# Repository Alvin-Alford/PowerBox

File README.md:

#  PowerBox

> An all-in-one power solution for cyberdecks and portable embedded systems.

PowerBox is my custom-designed PCB that handles USB-C Power Delivery input, dual-cell lithium battery management, balance charging, and regulated power output, all in a single compact board. Designed to push up to **36W** of power to whatever you throw at it.

---

## Overview

*PowerBox was built to power DIY cyberdecks and portable computing projects that need more juice than a standard battery banks can provide.*

---

## Components

PowerBox is built around **7 core subsystems**:

### 1. USB-C Power Delivery Input
A USB-C port paired with a **PD sink controller** that negotiates **12V** from a PD-capable charger. At full load the circuit can draw up to **36W** which is well beyond what standard 5V USB can supply.

### 2. Dual Buck DC-DC Converters (×2)
Two **TPS54620** synchronous step-down converters provide regulated output voltages. The TPS54620 is a 6A, 17V capable device giving plenty of headroom for demanding loads.

### 3. Ideal Diode Circuits (×2)
When USB-C power is present, the battery-fed bucks are switched off to prevent backfeeding the charger. This creates a condition where the buck converter inputs can see negative voltages which is outside their rated range. The ideal diode circuits clamp this safely, acting as electronic diodes with near-zero forward voltage drop.

### 4. BMS Circuit (DW01A)
A battery management system built around the **DW01A** which is a popular and proven lithium-ion protection IC. Handles over-charge, over-discharge, and short-circuit protection for the cell pack.

### 5. 2S Balance Charger (BQ2588RGER)
A proper **2-series balance charger** using TI's **BQ2588RGER**, capable of up to **2A** charge current. Keeps both cells at equal state-of-charge for longevity and safety.

---

##  PCB

The PCB design files are in the [`PowerBox_PCB/`](./PowerBox_PCB) directory. Output gerbers and fabrication files are in [`Output/`](./Output).

---

## Design Logic

```
USB-C PD (12V, 36W)
        │
        ├──► Buck 1 (TPS54620) ──► Ideal Diode ──► Output Rail A
        │
        ├──► Buck 2 (TPS54620) ──► Ideal Diode ──► Output Rail B
        │
        └──► BQ2588RGER Balance Charger ──► 2S Li-Ion Pack
                                                  │
                                              DW01A BMS
                                                  │
                                            Battery Output
```

**Why did I choose 36W / USB-C PD?**

A 2S lithium pack needs to charge while simultaneously powering the system. At full system load, 15W standard USB-C isn't enough, it can't even charge an open MacBook. Requesting **12V via PD** and pulling up to **3A** gives the 36W headroom needed to charge the battery *and* run the load at the same time.

**Why two cells?**

More cells = more capacity. More capacity = the circuit can sustain high loads without the cells entering stress territory. A single-cell design at 36W draw would be asking for trouble (and possibly a fire).

---

## Repository Structure

```
PowerBox/
├── Notes/           # Design notes and calculations
├── Output/          # Gerber files and fabrication outputs
├── Parts/           # Bill of materials and component info
└── PowerBox_PCB/    # KiCad / PCB design files
```

---

## Key ICs

| Component | Part Number | Function |
|-----------|------------|----------|
| Buck Converter | TPS54620 | 6A, 17V synchronous step-down |
| Balance Charger | BQ2588RGER | 2S Li-Ion balance charger, 2A |
| BMS Controller | DW01A | Li-Ion protection IC |
| PD Sink | *(see Parts/)* | USB-C PD 12V negotiation |

---

## Zine

---

## License

See [LICENSE](./LICENSE) for details.

---

*Built by [Alvin-Alford](https://github.com/Alvin-Alford)*

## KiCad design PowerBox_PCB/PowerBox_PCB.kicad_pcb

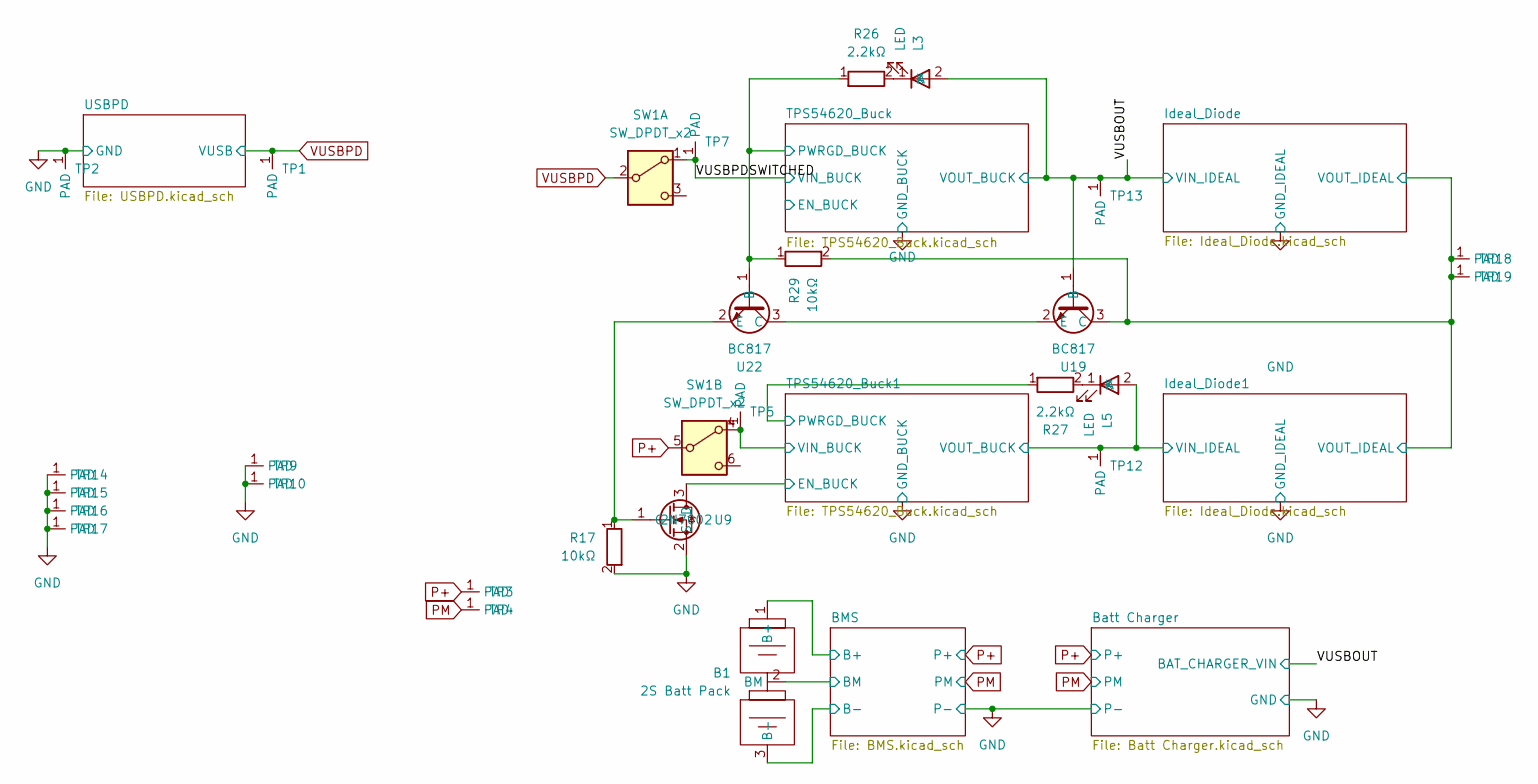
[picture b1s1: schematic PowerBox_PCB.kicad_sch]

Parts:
B1: 2S Batt Pack
L3, L5: LED; LED_0805_2012Metric_Pad1.15x1.40mm_HandSolder
R17, R29: 10kΩ; R_0805_2012Metric_Pad1.20x1.40mm_HandSolder
R26, R27: 2.2kΩ; R_0805_2012Metric_Pad1.20x1.40mm_HandSolder
SW1: SW_DPDT_x2; SwitchPads
TP1, TP2, TP3, TP4, TP5, TP7, TP9, TP10, TP12, TP13: PAD-2x2
TP14, TP15, TP16, TP17: M3-Pad
TP18, TP19: PAD-2x2-ThroughHole
U9: 2N7002; SOT-23
U19, U22: BC817; SOT-23

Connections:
/BMS/B-: B1.3 (B-); also elsewhere on the board
/BMS/BM: B1.2 (BM); also elsewhere on the board
/Ideal_Diode1/VIN_IDEAL: L5.2 (A), TP12.1 (PAD_1); also elsewhere on the board
/Ideal_Diode/VOUT_IDEAL: R29.2, TP18.1 (PAD_1), TP19.1 (PAD_1), U19.3 (C); also elsewhere on the board
/TPS54620_Buck1/EN_BUCK: U9.3 (D); also elsewhere on the board
/TPS54620_Buck1/PWRGD_BUCK: R27.1; also elsewhere on the board
/TPS54620_Buck1/VIN_BUCK: SW1.4 (A), TP5.1 (PAD_1); also elsewhere on the board
/TPS54620_Buck/PWRGD_BUCK: R26.1, R29.1, U22.1 (B); also elsewhere on the board
/VUSBOUT: L3.2 (A), TP13.1 (PAD_1), U19.1 (B); also elsewhere on the board
/VUSBPDSWITCHED: SW1.1 (A), TP7.1 (PAD_1); also elsewhere on the board
GND: R17.2, TP2.1 (PAD_1), TP9.1 (PAD_1), TP10.1 (PAD_1), TP14.1 (PAD_1), TP15.1 (PAD_1), TP16.1 (PAD_1), TP17.1 (PAD_1), U9.2 (S); also elsewhere on the board
unnamed: L3.1 (K), R26.2
unnamed: L5.1 (K), R27.2
unnamed: U19.2 (E), U22.3 (C)
unnamed: R17.1, U9.1 (G), U22.2 (E)
P+: B1.1 (B+), SW1.5 (B), TP3.1 (PAD_1); also elsewhere on the board
PM: TP4.1 (PAD_1); also elsewhere on the board
VUSBPD: SW1.2 (B), TP1.1 (PAD_1); also elsewhere on the board

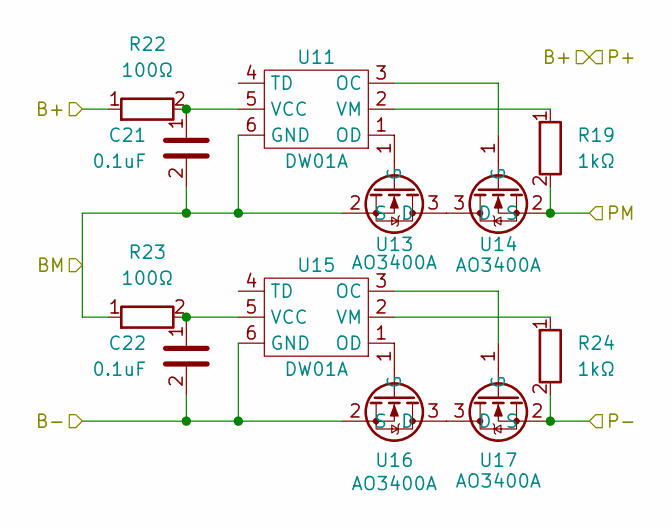
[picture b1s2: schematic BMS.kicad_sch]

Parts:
C21, C22: 0.1uF; C_0805_2012Metric_Pad1.18x1.45mm_HandSolder
R19, R24: 1kΩ; R_0805_2012Metric_Pad1.20x1.40mm_HandSolder
R22, R23: 100Ω; R_0805_2012Metric_Pad1.20x1.40mm_HandSolder
U11, U15: DW01A; SOT-23-6_Handsoldering
U13, U14, U16, U17: AO3400A; SOT-23_Handsoldering

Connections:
/BMS/B-: C22.2, U15.6 (GND), U16.2 (S); also elsewhere on the board
/BMS/BM: C21.2, R23.1, U11.6 (GND), U13.2 (S); also elsewhere on the board
GND: R24.2, U17.2 (S); also elsewhere on the board
unnamed: U11.3 (OC), U14.1 (G)
unnamed: U11.1 (OD), U13.1 (G)
unnamed: C21.1, R22.2, U11.5 (VCC)
unnamed: R19.1, U11.2 (VM)
unnamed: U13.3 (D), U14.3 (D)
unnamed: U15.3 (OC), U17.1 (G)
unnamed: U15.1 (OD), U16.1 (G)
unnamed: C22.1, R23.2, U15.5 (VCC)
unnamed: R24.1, U15.2 (VM)
unnamed: U16.3 (D), U17.3 (D)
P+: R22.1; also elsewhere on the board
PM: R19.2, U14.2 (S); also elsewhere on the board

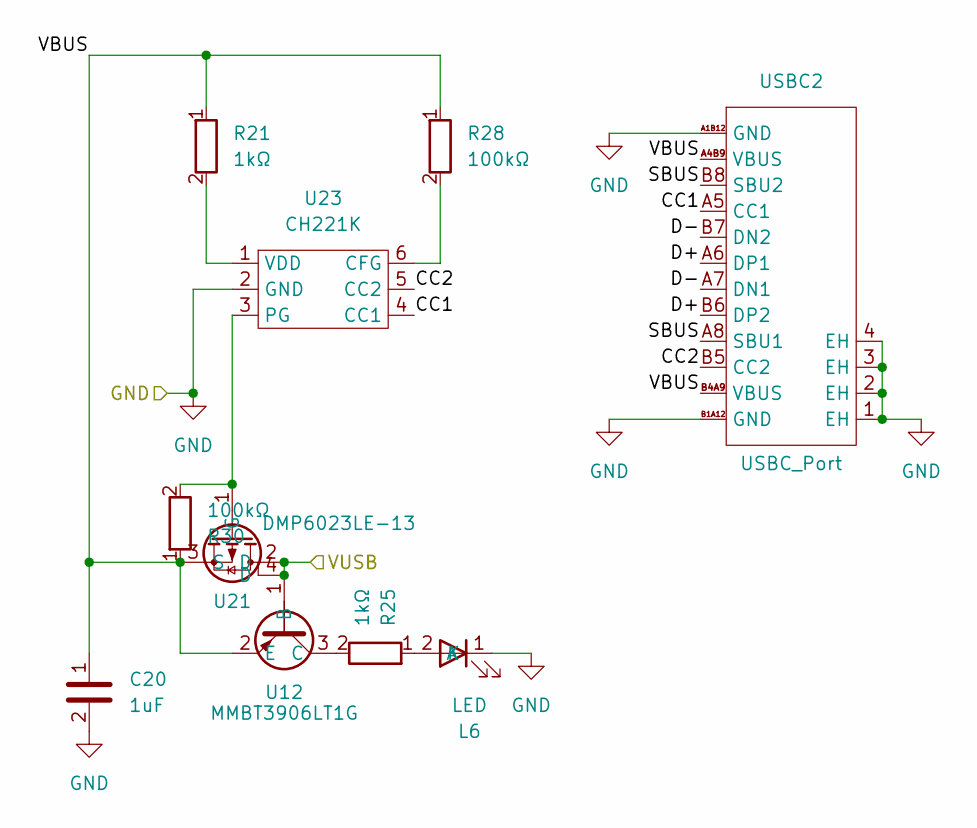
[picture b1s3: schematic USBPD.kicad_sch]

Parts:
C20: 1uF; C_0805_2012Metric_Pad1.18x1.45mm_HandSolder
L6: LED; LED_0805_2012Metric_Pad1.15x1.40mm_HandSolder
R21, R25: 1kΩ; R_0805_2012Metric_Pad1.20x1.40mm_HandSolder
R28, R30: 100kΩ; R_0805_2012Metric_Pad1.20x1.40mm_HandSolder
U12: MMBT3906LT1G; SOT-23
U21: DMP6023LE-13; SOT-223
U23: CH221K; SOT-23-6
USBC2: USBC_Port; USB-C_SMD-TYPE-C-31-M-12_1; Manufacturer Part TYPE-C-31-M-12; LCSC Part Name Type-C 母 卧贴

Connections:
/USBPD/CC1: U23.4 (CC1), USBC2.A5 (CC1)
/USBPD/CC2: U23.5 (CC2), USBC2.B5 (CC2)
/USBPD/D+: USBC2.A6 (DP1), USBC2.B6 (DP2)
/USBPD/D-: USBC2.A7 (DN1), USBC2.B7 (DN2)
/USBPD/SBUS: USBC2.A8 (SBU1), USBC2.B8 (SBU2)
/USBPD/VBUS: C20.1, R21.1, R28.1, R30.1, U12.2 (E), U21.3 (S), USBC2.A4B9 (VBUS), USBC2.B4A9 (VBUS)
GND: C20.2, L6.1 (K), U23.2 (GND), USBC2.1 (EH), USBC2.2 (EH), USBC2.3 (EH), USBC2.4 (EH), USBC2.A1B12 (GND), USBC2.B1A12 (GND); also elsewhere on the board
unnamed: L6.2 (A), R25.1
unnamed: R25.2, U12.3 (C)
unnamed: R30.2, U21.1 (G), U23.3 (PG)
unnamed: R28.2, U23.6 (CFG)
unnamed: R21.2, U23.1 (VDD)
VUSBPD: U12.1 (B), U21.2 (D), U21.4 (D); also elsewhere on the board

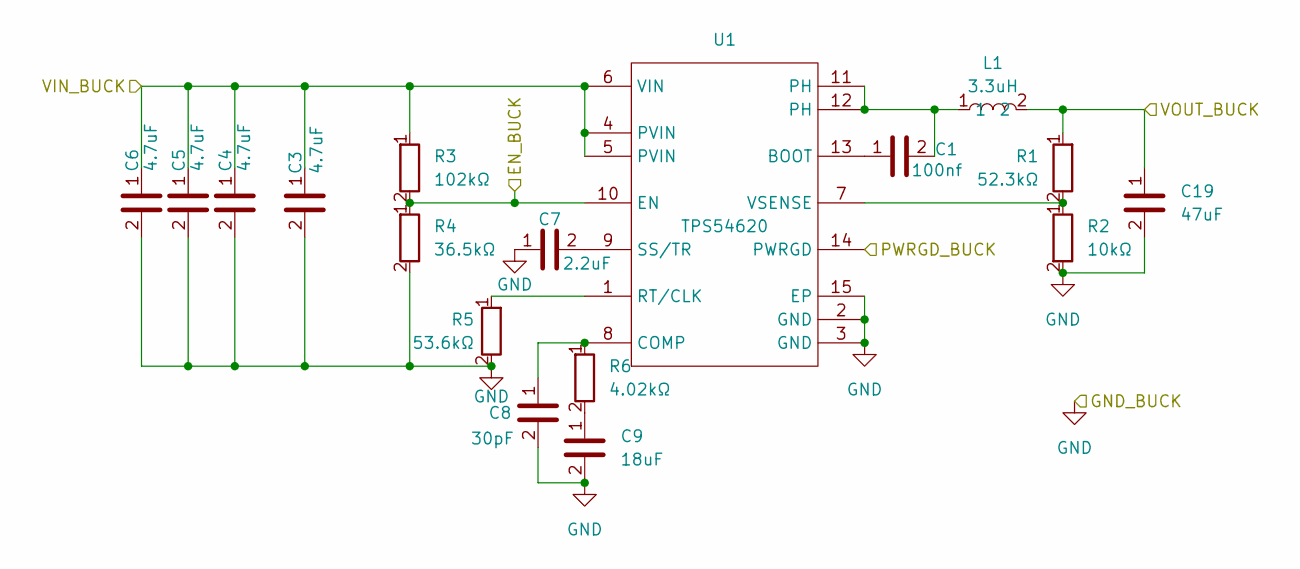
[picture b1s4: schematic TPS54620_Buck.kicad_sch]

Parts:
C1: 100nf; C_0805_2012Metric_Pad1.18x1.45mm_HandSolder
C3, C4, C5, C6: 4.7uF; C_0805_2012Metric_Pad1.18x1.45mm_HandSolder
C7: 2.2uF; C_0805_2012Metric_Pad1.18x1.45mm_HandSolder
C8: 30pF; C_0805_2012Metric_Pad1.18x1.45mm_HandSolder
C9: 18uF; C_0805_2012Metric_Pad1.18x1.45mm_HandSolder
C19: 47uF; C_1210_3225Metric_Pad1.33x2.70mm_HandSolder
L1: 3.3uH; IND-SMD_L8.5-W8.0_PSPMAA0803H-330M-ANP
R1: 52.3kΩ; R_0805_2012Metric_Pad1.20x1.40mm_HandSolder
R2: 10kΩ; R_0805_2012Metric_Pad1.20x1.40mm_HandSolder
R3: 102kΩ; R_0805_2012Metric_Pad1.20x1.40mm_HandSolder
R4: 36.5kΩ; R_0805_2012Metric_Pad1.20x1.40mm_HandSolder
R5: 53.6kΩ; R_0805_2012Metric_Pad1.20x1.40mm_HandSolder
R6: 4.02kΩ; R_0805_2012Metric_Pad1.20x1.40mm_HandSolder
U1: TPS54620; VQFN-14_L3.5-W3.5-P0.50-TL-EP_TPS54622RHLT; Manufacturer Part TPS54620RHLR; LCSC Part Name 17V输入6A同步降压转换器

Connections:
/TPS54620_Buck/EN_BUCK: R3.2, R4.1, U1.10 (EN)
/TPS54620_Buck/PWRGD_BUCK: U1.14 (PWRGD); also elsewhere on the board
/VUSBOUT: C19.1, L1.2, R1.1; also elsewhere on the board
/VUSBPDSWITCHED: C3.1, C4.1, C5.1, C6.1, R3.1, U1.4 (PVIN), U1.5 (PVIN), U1.6 (VIN); also elsewhere on the board
GND: C3.2, C4.2, C5.2, C6.2, C7.1, C8.2, C9.2, C19.2, R2.2, R4.2, R5.2, U1.2 (GND), U1.3 (GND), U1.15 (EP); also elsewhere on the board
unnamed: C1.2, L1.1, U1.11 (PH), U1.12 (PH)
unnamed: C9.1, R6.2
unnamed: C1.1, U1.13 (BOOT)
unnamed: C8.1, R6.1, U1.8 (COMP)
unnamed: R5.1, U1.1 (RT/CLK)
unnamed: C7.2, U1.9 (SS/TR)
unnamed: R1.2, R2.1, U1.7 (VSENSE)

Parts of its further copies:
C10, C11, C12, C13: 4.7uF; C_0805_2012Metric_Pad1.18x1.45mm_HandSolder
C14: 30pF; C_0805_2012Metric_Pad1.18x1.45mm_HandSolder
C15: 2.2uF; C_0805_2012Metric_Pad1.18x1.45mm_HandSolder
C16: 18uF; C_0805_2012Metric_Pad1.18x1.45mm_HandSolder
C17: 100nf; C_0805_2012Metric_Pad1.18x1.45mm_HandSolder
C23: 47uF; C_1210_3225Metric_Pad1.33x2.70mm_HandSolder
L2: 3.3uH; IND-SMD_L8.5-W8.0_PSPMAA0803H-330M-ANP
R9: 102kΩ; R_0805_2012Metric_Pad1.20x1.40mm_HandSolder
R10: 36.5kΩ; R_0805_2012Metric_Pad1.20x1.40mm_HandSolder
R11: 53.6kΩ; R_0805_2012Metric_Pad1.20x1.40mm_HandSolder
R12: 4.02kΩ; R_0805_2012Metric_Pad1.20x1.40mm_HandSolder
R13: 52.3kΩ; R_0805_2012Metric_Pad1.20x1.40mm_HandSolder
R14: 10kΩ; R_0805_2012Metric_Pad1.20x1.40mm_HandSolder
U5: TPS54620; VQFN-14_L3.5-W3.5-P0.50-TL-EP_TPS54622RHLT; Manufacturer Part TPS54620RHLR; LCSC Part Name 17V输入6A同步降压转换器

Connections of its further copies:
/Ideal_Diode1/VIN_IDEAL: C23.1, L2.2, R13.1; also elsewhere on the board
/TPS54620_Buck1/EN_BUCK: R9.2, R10.1, U5.10 (EN); also elsewhere on the board
/TPS54620_Buck1/PWRGD_BUCK: U5.14 (PWRGD); also elsewhere on the board
/TPS54620_Buck1/VIN_BUCK: C10.1, C11.1, C12.1, C13.1, R9.1, U5.4 (PVIN), U5.5 (PVIN), U5.6 (VIN); also elsewhere on the board
GND: C10.2, C11.2, C12.2, C13.2, C14.2, C15.1, C16.2, C23.2, R10.2, R11.2, R14.2, U5.2 (GND), U5.3 (GND), U5.15 (EP); also elsewhere on the board
unnamed: C16.1, R12.2
unnamed: C17.2, L2.1, U5.11 (PH), U5.12 (PH)
unnamed: C17.1, U5.13 (BOOT)
unnamed: C14.1, R12.1, U5.8 (COMP)
unnamed: R11.1, U5.1 (RT/CLK)
unnamed: C15.2, U5.9 (SS/TR)
unnamed: R13.2, R14.1, U5.7 (VSENSE)

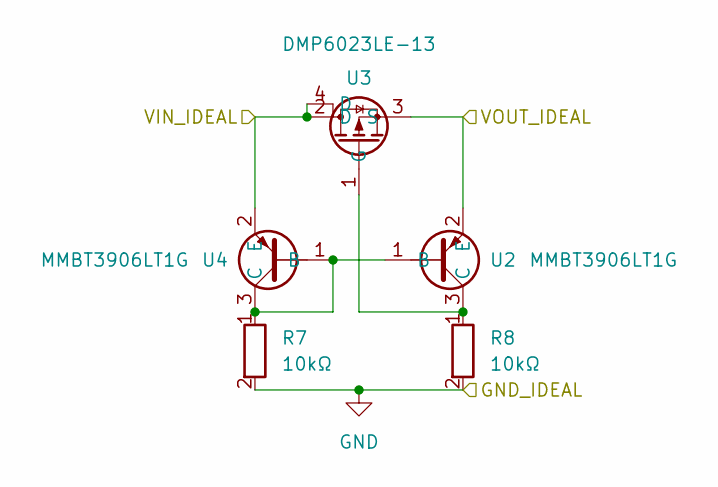
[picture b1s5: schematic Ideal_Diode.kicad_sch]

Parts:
R7, R8: 10kΩ; R_0805_2012Metric_Pad1.20x1.40mm_HandSolder
U2, U4: MMBT3906LT1G; SOT-23
U3: DMP6023LE-13; SOT-223

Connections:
/Ideal_Diode/VOUT_IDEAL: U2.2 (E), U3.3 (S); also elsewhere on the board
/VUSBOUT: U3.2 (D), U3.4 (D), U4.2 (E); also elsewhere on the board
GND: R7.2, R8.2; also elsewhere on the board
unnamed: R7.1, U2.1 (B), U4.1 (B), U4.3 (C)
unnamed: R8.1, U2.3 (C), U3.1 (G)

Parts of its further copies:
R15, R16: 10kΩ; R_0805_2012Metric_Pad1.20x1.40mm_HandSolder
U6, U8: MMBT3906LT1G; SOT-23
U7: DMP6023LE-13; SOT-223

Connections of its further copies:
/Ideal_Diode1/VIN_IDEAL: U6.2 (E), U7.2 (D), U7.4 (D); also elsewhere on the board
/Ideal_Diode/VOUT_IDEAL: U7.3 (S), U8.2 (E); also elsewhere on the board
GND: R15.2, R16.2; also elsewhere on the board
unnamed: R15.1, U6.1 (B), U6.3 (C), U8.1 (B)
unnamed: R16.1, U7.1 (G), U8.3 (C)

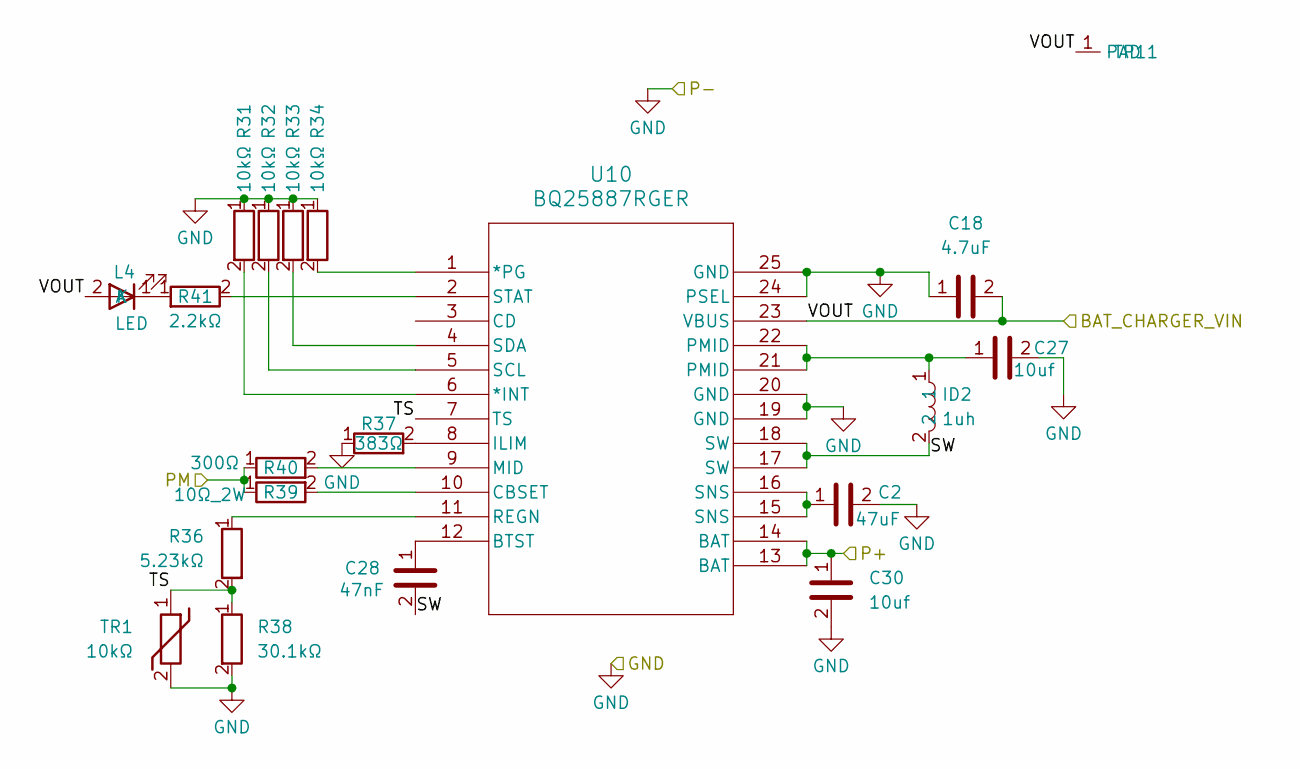
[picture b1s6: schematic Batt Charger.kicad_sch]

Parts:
C2: 47uF; C_1210_3225Metric_Pad1.33x2.70mm_HandSolder
C18: 4.7uF; C_0805_2012Metric_Pad1.18x1.45mm_HandSolder
C27, C30: 10uf; C_0805_2012Metric_Pad1.18x1.45mm_HandSolder
C28: 47nF; C_0805_2012Metric_Pad1.18x1.45mm_HandSolder
ID2: 1uh; L_1008_2520Metric_Pad1.43x2.20mm_HandSolder
L4: LED; LED_0805_2012Metric_Pad1.15x1.40mm_HandSolder
R31, R32, R33, R34: 10kΩ; R_0805_2012Metric_Pad1.20x1.40mm_HandSolder
R36: 5.23kΩ; C_0805_2012Metric_Pad1.18x1.45mm_HandSolder
R37: 383Ω; C_0805_2012Metric_Pad1.18x1.45mm_HandSolder
R38: 30.1kΩ; C_0805_2012Metric_Pad1.18x1.45mm_HandSolder
R39: 10Ω_2W; R_2512_6332Metric_Pad1.40x3.35mm_HandSolder
R40: 300Ω; R_0805_2012Metric_Pad1.20x1.40mm_HandSolder
R41: 2.2kΩ; R_0805_2012Metric_Pad1.20x1.40mm_HandSolder
TP11: PAD-2x2
TR1: 10kΩ; ThermistorPads
U10: BQ25887RGER; VQFN24_RGE_TEX

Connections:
/Batt Charger/SW: C28.2, ID2.2, U10.17 (SW), U10.18 (SW)
/Batt Charger/TS: R36.2, R38.1, TR1.1, U10.7 (TS)
/VUSBOUT: C18.2, L4.2 (A), TP11.1 (PAD_1), U10.23 (VBUS); also elsewhere on the board
GND: C2.2, C18.1, C27.2, C30.2, R31.1, R32.1, R33.1, R34.1, R37.1, R38.2, TR1.2, U10.19 (GND), U10.20 (GND), U10.24 (PSEL), U10.25 (GND); also elsewhere on the board
unnamed: C2.1, U10.15 (SNS), U10.16 (SNS)
unnamed: C27.1, ID2.1, U10.21 (PMID), U10.22 (PMID)
unnamed: L4.1 (K), R41.1
unnamed: R31.2, U10.6 (*INT)
unnamed: R34.2, U10.1 (*PG)
unnamed: C28.1, U10.12 (BTST)
unnamed: R39.2, U10.10 (CBSET)
unnamed: R37.2, U10.8 (ILIM)
unnamed: R40.2, U10.9 (MID)
unnamed: R36.1, U10.11 (REGN)
unnamed: R32.2, U10.5 (SCL)
unnamed: R33.2, U10.4 (SDA)
unnamed: R41.2, U10.2 (STAT)
P+: C30.1, U10.13 (BAT), U10.14 (BAT); also elsewhere on the board
PM: R39.1, R40.1; also elsewhere on the board

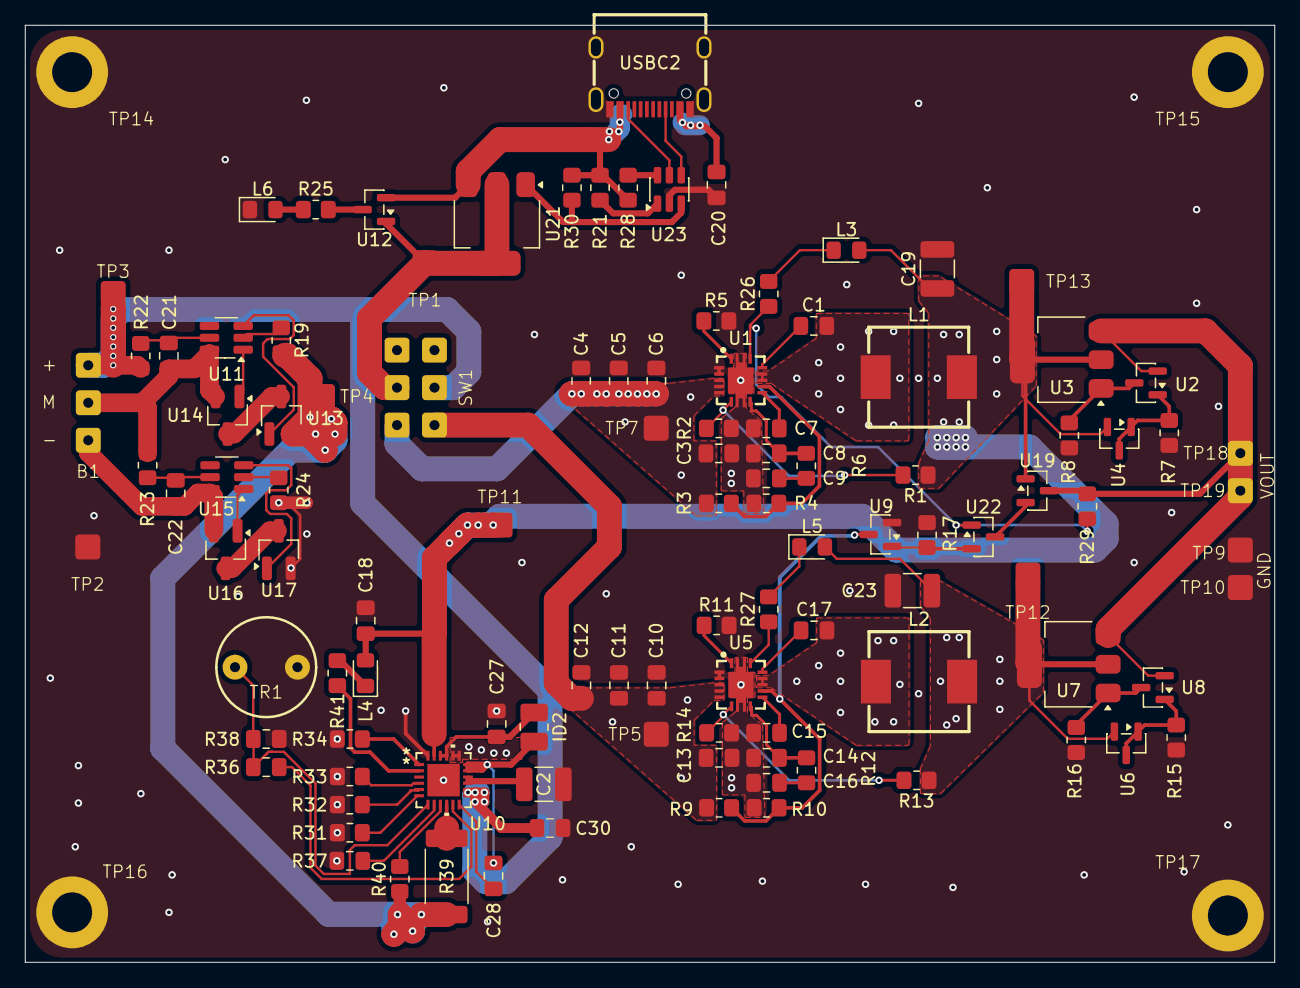
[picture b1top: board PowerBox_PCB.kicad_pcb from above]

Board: 2 copper layers, 100.0 x 75.0 mm, 113 parts (0 on the bottom side), 73 nets.

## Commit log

2026-05-21 Added footprints
    Added footprints i made for a earlier project
2026-05-24 Added Powersupplys
    Added the TPS54620 as powersupplys and built circuit for it.
    Added A LDO 5v 3A DC-DC VREG for the battery charger
2026-05-24 Added USBPD & BMD & BATTCHARGER
    Added USBPD & BMD & BATTCHARGER
2026-05-25 Finished
    Basically done
2026-05-25 pluh
2026-05-27 e
    e
2026-05-27 add indicator lights
    add indicator lights
2026-05-27 add more stuff for shipping
2026-05-27 Improve readme
2026-05-27 fix readme
2026-05-27 added zine
2026-05-27 add zine
2026-05-27 zine
2026-05-27 made step model
2026-05-27 fixed 3d stuff
2026-05-27 more model shenaigans
2026-05-28 made board a lot smaller
    board is now 100 x 75 mm
2026-05-28 added all models
2026-05-28 remodel
2026-05-28 Fixes
    Fixed model paths,
    Closed to prevent still open another device warning
2026-05-28 fix more relative paths
2026-06-01 added schematics as pdf
2026-06-02 fix bom
    bom
2026-06-11 Changed HUSB238 to CH221K
    HUSB238 Went out of stock so changed to CH221K
2026-06-11 saved
2026-06-14 i finished and getting it made

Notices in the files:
PowerBox_PCB/PowerBox_PCB.kicad_pcb:
© CC-BY-NC-SA 4.0 Alvin Alford
